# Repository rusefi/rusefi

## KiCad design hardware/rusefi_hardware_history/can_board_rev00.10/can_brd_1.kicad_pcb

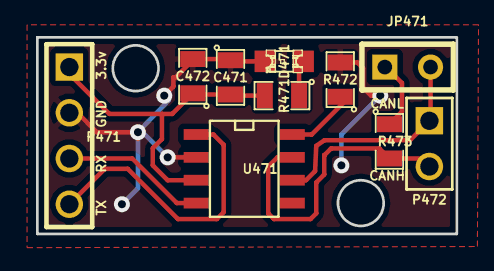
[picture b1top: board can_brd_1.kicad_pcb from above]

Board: 2 copper layers, 23.3 x 10.9 mm, 11 parts (1 on the bottom side), 9 nets.

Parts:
C471: .1uF; SM0805
C472: 4.7uF; SM0805
D471: RED; LED-0805
G471: LOGO; LOGO_F
JP471: JUMPER; SIL-2
P471: CONN_4; PIN_ARRAY_4x1
P472: CONN_2; PIN_ARRAY_2_A
R471: 1k; SM0805
R472: 10k; SM0805
R473: 120; SM0805
U471: SN65HVD230; SO8E

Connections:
/3.3V: C471.2, C472.1, P471.1, R471.2, U471.3
/CANH: P472.2, R473.2, U471.7
/CANL: JP471.2, P472.1, U471.6
/CAN_RX: P471.3, U471.4
/CAN_TX: P471.4, U471.1
GND: C471.1, C472.2, D471.2, P471.2, R472.2, U471.2
unnamed: R472.1, U471.8
unnamed: JP471.1, R473.1
unnamed: D471.1, R471.1

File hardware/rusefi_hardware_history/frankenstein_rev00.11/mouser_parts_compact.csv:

### this file was generated by rusEfi bom_builder on Sat Mar 08 11:58:11 CST 2014
### 292 components in 2047 lines of frankenstein.cmp
### 65 kinds of components in input file
### 5 entries in BOM dictionary bom_dictionary_mouser.csv
### 0 entries in ignore list
### no BOM record for 1pin_CONN_1
### no BOM record for LED-0805_GREEN
### no BOM record for LED-0805_LED
### no BOM record for LED-0805_RED
### no BOM record for LED-1206_LED
### no BOM record for LOGO_F_LOGO
### no BOM record for LOGO_LOGO
### no BOM record for MICRO-SDCARD-CONNECTOR-3300060P1_MICRO-SDCARD-CONNECTOR-3300060P1
### no BOM record for OSTVN06A150_CONN_6
### no BOM record for PIN_ARRAY-6X1_CONN_6
### no BOM record for PIN_ARRAY_10X2_CONN_10X2
### no BOM record for PIN_ARRAY_10X2_M_CONN_10X2
### no BOM record for PIN_ARRAY_1_CONN_1
### no BOM record for PIN_ARRAY_2X1_CONN_2
### no BOM record for PIN_ARRAY_2_A_CONN_2
### no BOM record for PIN_ARRAY_2_A_JUMPER
### no BOM record for PIN_ARRAY_3X1_CONN_3
### no BOM record for PIN_ARRAY_3_A_CONN_3
### no BOM record for PIN_ARRAY_4x1_CONN_4
### no BOM record for PIN_ARRAY_5x2_CONN_5X2
### no BOM record for SIL-16_3.5MM_CONN_16
### no BOM record for SIL-2_0R
### no BOM record for SIL-2_CONN_2
### no BOM record for SIL-2_DIODE
### no BOM record for SIL-2_JUMPER
### no BOM record for SIL-2_OPT
### no BOM record for SIL-2_TEST
### no BOM record for SM0805_.1uF
### no BOM record for SM0805_0.01uF
### no BOM record for SM0805_0.1uF
### no BOM record for SM0805_100
### no BOM record for SM0805_1000pF
### no BOM record for SM0805_10K
### no BOM record for SM0805_10k
### no BOM record for SM0805_10uF
### no BOM record for SM0805_120
### no BOM record for SM0805_1500
### no BOM record for SM0805_1K
### no BOM record for SM0805_1M
### no BOM record for SM0805_1k
### no BOM record for SM0805_1uF
### no BOM record for SM0805_20K
### no BOM record for SM0805_20R
### no BOM record for SM0805_2700
### no BOM record for SM0805_4.7uF
### no BOM record for SM0805_4700pF
### no BOM record for SM0805_47pF
### no BOM record for SM0805_500K
### no BOM record for SM0805_5k
### no BOM record for SM0805_LED
### no BOM record for SM1206_LED
### no BOM record for SO8E_ST_OVP_DRIVER
### no BOM record for SOD-123_DIODE
### no BOM record for bornier3_CONN_3
### no BOM record for msoic-8_TC4427AVOA
### no BOM record for pin_array_10x2_CONN_10X2
### no BOM record for pin_array_3x2_CONN_3X2
### no BOM record for pin_array_4x2_CONN_4X2
### no BOM record for sot23_DOUBLE_SCHOTTKY
### no BOM record for uMAX-uSOP_10_MAX9939




1,656-DX2R005HN2E700,mini USB socket
1,296-11654-1-ND,CAN driver
1,700-MAX9926UAEE,VR chip
3,595-LMV324IDR,quad op-amp
1,895-FT232RL,USB TTL chip

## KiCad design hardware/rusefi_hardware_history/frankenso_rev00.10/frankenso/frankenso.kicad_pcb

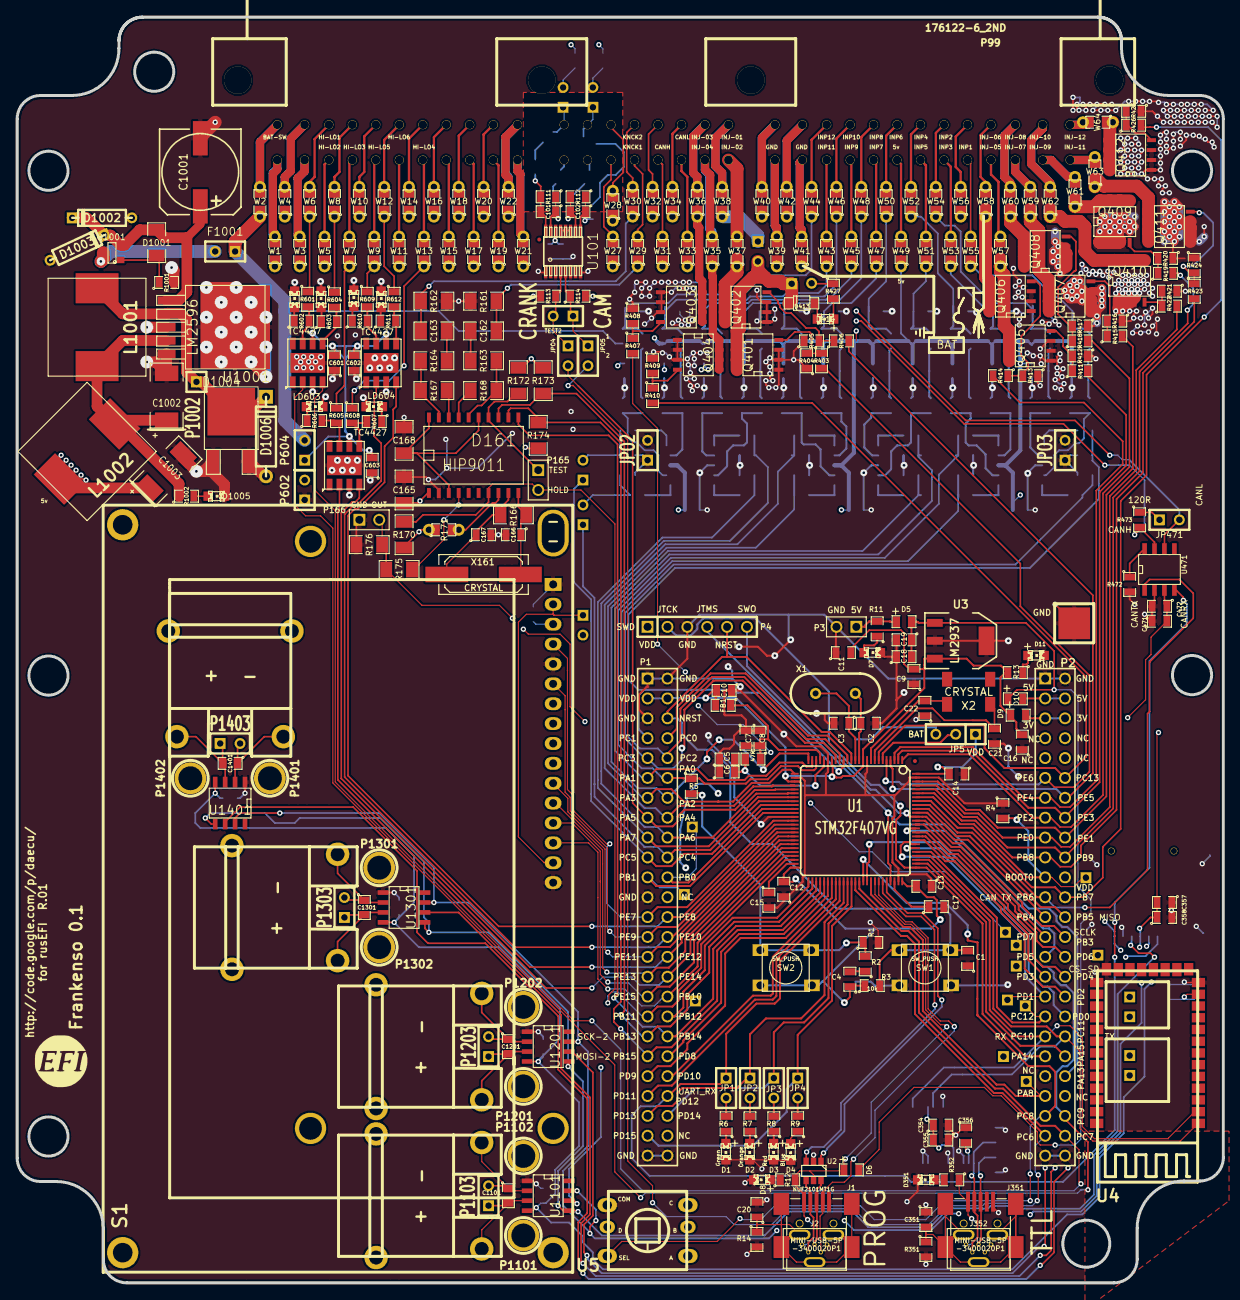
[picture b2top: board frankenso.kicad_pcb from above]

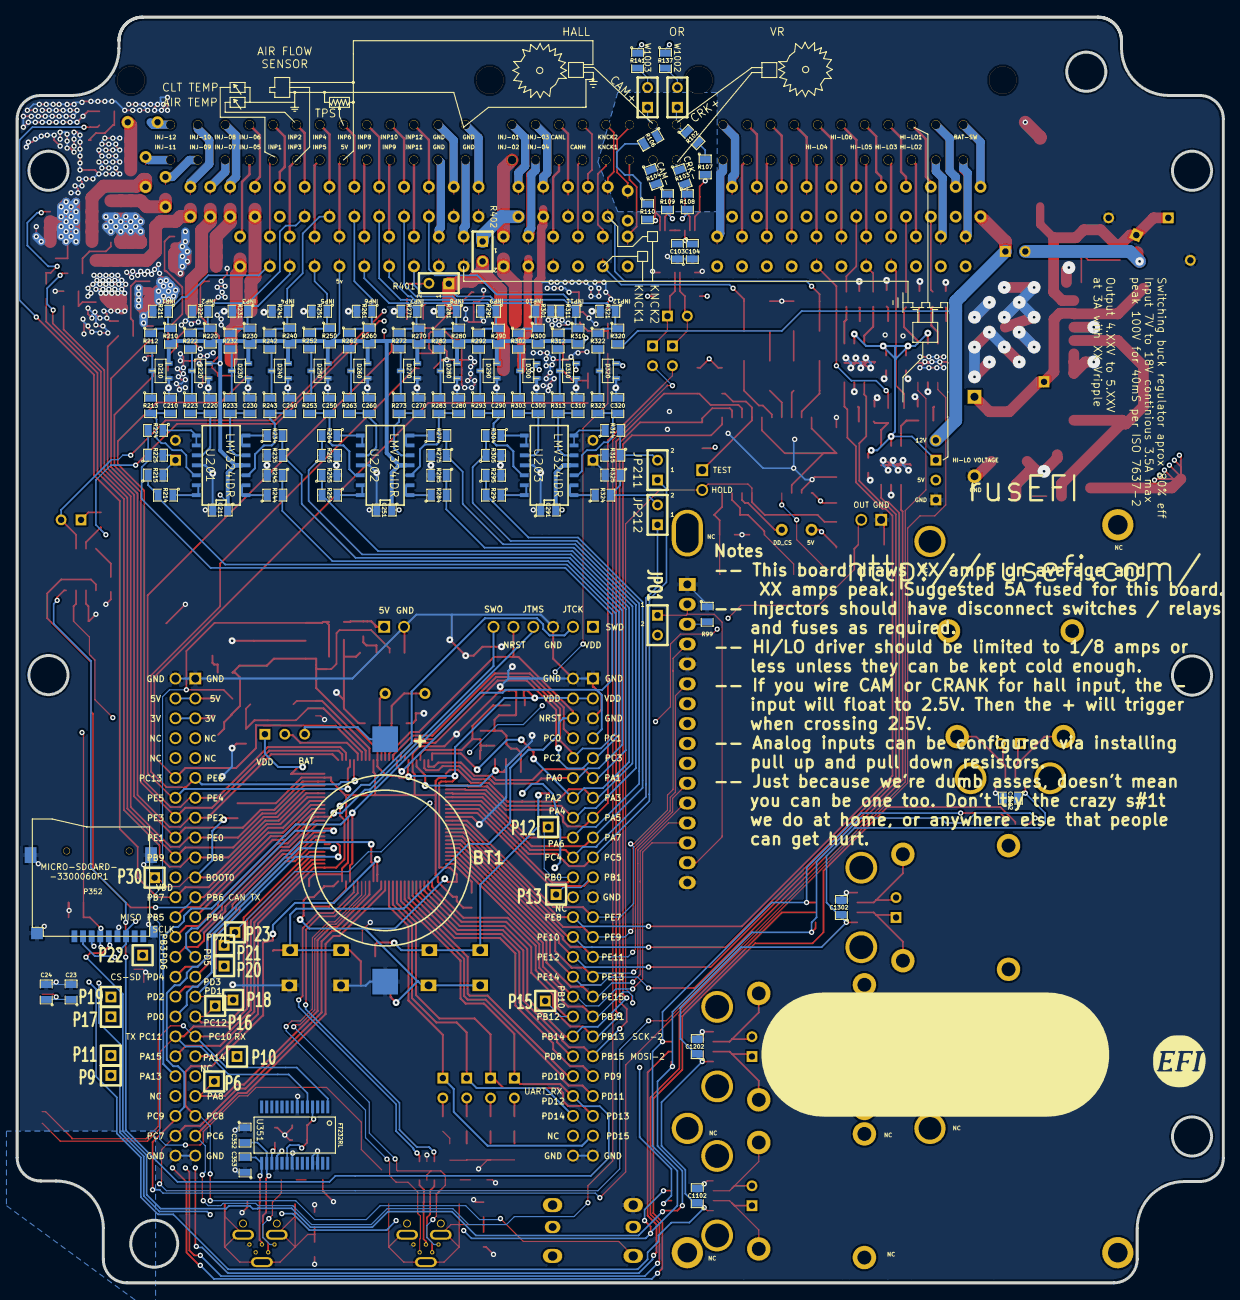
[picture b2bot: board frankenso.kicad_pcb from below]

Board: 4 copper layers, 154.1 x 161.7 mm, 441 parts (150 on the bottom side), 324 nets.

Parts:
BT1: BATTERY_CR2032; BATT_CR2032_MPD
C1: 0.02uF; SM0805
C2, C3, C21, C22: 18pF; SM0805
C4, C15, C17: 2u2F; SM0805
C5, C8, C210, C220, C230, C240, C250, C260, C270, C280, C290, C300, C310, C320: 0.01uF; SM0805
C6, C7, C16, C23: 1uF; SM0805
C9, C10, C11, C12, C13, C14, C18, C20, C104, C211, C251, C291, C601, C602, C603: 0.1uF; SM0805
C19, C354, C358, C472: 4.7uF; SM0805
C24, C355, C356, C357, C471: .1uF; SM0805
C101, C102: 1000pF; SM0805
C103: 10uF; SM0805
C162, C163: 47n; SM1206
C165: 100n; SM1206
C166, C167: 20pF; SM0805
C168: 22n; SM1206
C351: 4700pF; SM0805
C352, C353: 47pF; SM0805
C1001: 470uF 25V; SMDSVP10
C1002, C1003: 220uF 16V; SM2512
C1101, C1201, C1301, C1401: 10nF; SM0805-SM0603
C1102, C1202, C1302, C1402: 100nF; SM0805-SM0603
D1, D2, D3, D4, D7, D8, D11, D414: LED_0805; LED-0805_A
D5, D6, D9, D10: DIODESCH; SM0805-diode
D161: HIP9011; SO20L
D210, D220, D230, D240, D250, D260, D270, D280, D290, D300, D310, D320: DOUBLE_SCHOTTKY; sot23
D351: GREEN; LED-0805_A
D413: DIODE; SOD-123
D1001: ZENERSMALL; SM1206
D1002, D1003: TVS; D3
D1004: SCHDPAK; DPAK2
D1005: GREEN; LED-0805
D1006: DIODESCH; D4
F1001: 3.5A; SIL-2
FB1: FILTER; SM0805
G1: LOGO; LOGO_F
G2: LOGO
J1, J351: MINI-USB-5P-3400020P1
J2, J352: MINI-USB-5P-3400020P1; MINI-USB_RCTP_V-T_B
JP1, JP2, JP3, JP4, JP471: JUMPER; JUMPER-2
JP5: JUMPER3; SIL-3
JP211, JP212: TEST; SIL-2
JPO1, JPO2, JPO3, JPO4, JPO5: TEST; SIL-2
L1001, L1002: 38uH; SM100uH
LD601, LD602, LD603, LD604, LD605, LD606: LED; LED-0805
P1, P2: CONN_25X2; PIN_ARRAY_25x2_A
P3: CONN_2; PIN_ARRAY_2_A
P4: CONN_6; PIN_ARRAY-6X1
P5: CONN_1; 1PIN_SMD
P6, P9, P10, P11, P12, P13, P15, P16, P17, P18, P19, P20, P21, P22, P23, P30, P1002: CONN_1; SIL-1
P99: 176122-6_2ND; 176122-6_2nd
P165, P166: CONN_2; PIN_ARRAY_2X1
P352: MICRO-SDCARD-CONNECTOR-3300060P1
P602, P604, P1103, P1203, P1303, P1403: CONN_2; SIL-2
P1101, P1102, P1201, P1202, P1301, P1302, P1401, P1402: CONN_1; 1pin
P1104, P1204, P1304, P1404: CONN_2; tcpl_PCC-SMP
Q401, Q402, Q403, Q404, Q405, Q406, Q407, Q408, Q409, Q410, Q411, Q412: OVP_DRIVER; SO8E_ST
Q1001: MOS_PRO; SOT23
R1, R3, R4, R113, R114, R212, R222, R232, R242, R252, R262, R272, R282, R292, R302, R312, R321, R322, R472: 10k; SM0805
R2: 100R; SM0805
R5: 330R; SM0805
R6, R7, R8, R9: 680R; SM0805
R10: 47R; SM0805
R11, R12, R13, R352, R1001, R1002: 1k; SM0805
R14: 100k; SM0805
R99: 2K; SM0805
R102, R103, R104, R106, R107, R108, R109, R110, R111, R112: 5k; SM0805
R137, R141, R404, R405, R408, R409, R412, R413, R416, R417, R420, R421, R424, R425, R427: 1K; SM0805
R161, R162, R166: 1M; SM1206
R163, R164, R175, R176: 10k; SM1206
R167, R168: 68k; SM1206
R170, R172, R173, R174: 1K; SM1206
R171: 1K; SM0805_jumper
R210, R220, R230, R240, R250, R260, R270, R280, R290, R300, R310, R602, R603, R606, R607, R610, R611: 2700; SM0805
R211, R221, R231, R241, R251, R261, R271, R281, R291, R301, R311: 500K; SM0805
R213, R223, R233, R243, R253, R263, R273, R283, R293, R303, R313, R323, R601, R604, R605, R608, R609, R612: 100; SM0805
R214, R215, R224, R225, R234, R235, R244, R245, R254, R255, R264, R265, R274, R275, R284, R285, R294, R295, R304, R305, R314, R315, R324, R325: 1500; SM0805
R320: 39k; SM0805
R351: 1M; SM0805
R401: OPT; SIL-2
R402: 0R; SIL-2
R403, R406, R407, R410, R411, R414, R415, R418, R419, R422, R423, R426: 20R; SM0805
R473: 120; SM0805
S1: DISPLAY_BL; DISPLAY_4x20_BL
SW1, SW2: SW_PUSH; TL-1105
TEST2: TEST; SIL-2
U1: STM32F407VG; TQFP_100
U2: NUF2101MT1G; SOT-457
U3: LM2937; SOT223
U4: ITEAD_HC-0X; ITEAD_HC-05
U5: SKQUCAA010
U101: MAX9926/9927; maxim-10-QSOP16
U201, U202, U203: LMV324IDR; SO14N
U351: FT232RL; ssop-28
U471: SN65HVD230; SO8E
U601, U602, U603: TC4427; SOIC8-DFN
U1001: LM2596; DPAK5
U1101, U1201, U1301, U1401: MAX31855KASA; SO8E
W1, W2, W3, W4, W5, W6, W7, W8, W9, W10, W11, W12, W13, W14, W15, W16, W17, W18, W19, W20, W21, W22, W27, W28, W29, W30, W31, W32, W33, W34, W35, W36, W37, W38, W39, W40, W41, W42, W43, W44, W45, W46, W47, W48, W49, W50, W51, W52, W53, W54, W55, W56, W57, W58, W59, W60, W61, W62, W63, W64: TEST; SM0805_jumper
W1002, W1003: JMP; SIL-2
X1: CRYSTAL; HC-49V
X2: CRYSTAL; MC-306
X161: CRYSTAL; Q_49U3HMS

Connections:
/DD_HIP9011/5V: C4.1, C9.2, C10.2, C11.2, C12.2, C13.2, C14.2, C16.2, C23.1, C24.1, C103.2, C104.1, C165.1, C211.1, C251.1, C291.2, C354.1, C355.2, C1003.1, D9.1, D10.2, D161.1, D210.3, D220.3, D230.3, D240.3, D250.3, D260.3, D270.3, D280.3, D290.3, D300.3, D310.3, D320.3, FB1.2, JP5.1, JPO1.2, L1002.2, P1.3, P1.4, P2.3, P2.4, P2.22, P4.1, P602.2, R3.1, R13.2, R113.1, R114.2, R137.1, R141.1, R170.1, R171.1, R172.1, R173.1, R174.1, R210.2, R220.2, R230.2, R240.2, R250.2, R260.2, R270.2, R280.2, R290.2, R300.2, R310.2, SW2.2, U1.11, U1.19, U1.28, U1.50, U1.75, U1.100, U3.3, U4.12, U101.14, U201.4, U202.4, U203.4, U351.4, U351.20, W49.1
/DD_HIP9011/CS: D161.8, R171.2
/DD_HIP9011/INT/HLD: D161.7, P1.35, P165.2, R170.2, U1.48
/DD_HIP9011/INTOUT: D161.4, R175.1
/DD_HIP9011/KNOCK1: C162.1, R161.1, W29.1
/DD_HIP9011/KNOCK2: C163.1, R162.1, W30.1
/DD_HIP9011/OUT: P1.8, P166.2, R175.2, R176.1, U1.15
/DD_HIP9011/TEST: D161.14, P165.1, R172.2
/HD44780_VCC: JPO1.1, S1.2, S1.A
/PWR_buck_12V_switcher/FB: C1002.1, L1001.2, L1002.1, R1002.1, U1001.4
/PWR_buck_12V_switcher/OUT: D1004.2, D1006.2, L1001.1, P1002.1, U1001.2
/PWR_buck_12V_switcher/VBAT: C1001.1, D1001.2, D1002.2, D1003.2, Q1001.2, U1001.1
/PWR_buck_12V_switcher/Vf: F1001.2, Q1001.3
/adc_amp_divider/INP1: R210.1, R211.1, R212.1, W55.1
/adc_amp_divider/INP2: R220.1, R221.1, R222.1, W54.1
/adc_amp_divider/INP3: R230.1, R231.1, R232.1, W53.1
/adc_amp_divider/INP4: R240.1, R241.1, R242.1, W52.1
/adc_amp_divider/INP5: R250.1, R251.1, R252.1, W51.1
/adc_amp_divider/INP6: R260.1, R261.1, R262.1, W50.1
/adc_amp_divider/INP7: R270.1, R271.1, R272.1, W47.1
/adc_amp_divider/INP8: R280.1, R281.1, R282.1, W48.1
/adc_amp_divider/INP9: R290.1, R291.1, R292.1, W45.1
/adc_amp_divider/INP10: R300.1, R301.1, R302.1, W46.1
/adc_amp_divider/INP11: R310.1, R311.1, R312.1, W43.1
/adc_amp_divider/INP12: R320.1, R321.1, R322.1, W44.1
/adc_amp_divider/OUT1: P1.10, R214.2, R215.1, U1.17
/adc_amp_divider/OUT2: P1.7, R224.2, R225.1, U1.16
/adc_amp_divider/OUT3: P1.12, R5.1, R234.2, R235.1, U1.23
/adc_amp_divider/OUT4: P1.9, R244.2, R245.1, U1.18
/adc_amp_divider/OUT5: P1.14, R254.2, R255.1, U1.25
/adc_amp_divider/OUT6: P1.11, R264.2, R265.1, U1.24
/adc_amp_divider/OUT7: P1.16, R274.2, R275.1, U1.29
/adc_amp_divider/OUT8: P1.13, R284.2, R285.1, U1.26
/adc_amp_divider/OUT9: P1.17, R294.2, R295.1, U1.32
/adc_amp_divider/OUT10: P1.18, R304.2, R305.1, U1.31
/adc_amp_divider/OUT11: JP211.1, P1.19, U1.34
/adc_amp_divider/OUT12: JP212.1, P1.20, U1.33
/can_brd_1/3.3V: C357.2, C358.1, C471.2, C472.1, C1102.1, C1202.1, C1302.1, C1402.1, D9.2, P2.5, P2.6, P352.4, U471.3, U1101.4, U1201.4, U1301.4, U1401.4
/can_brd_1/CANH: R473.2, U471.7, W33.1
/can_brd_1/CANL: JP471.2, U471.6, W34.1
/can_brd_1/CAN_RX: JP1.1, P1.44, U1.59, U471.4
/can_brd_1/CAN_TX: P2.23, U1.92, U471.1
/cps_vrs_io_1/CAM: JPO5.1, R114.1, TEST2.1, U101.5
/cps_vrs_io_1/CAM+: P99.32, R106.1, W1003.1
/cps_vrs_io_1/CAM-: P99.24, R104.1
/cps_vrs_io_1/CRANK: JPO4.1, R113.2, TEST2.2, U101.4
/cps_vrs_io_1/CRK2+: P99.31, R102.1, W1002.1
/cps_vrs_io_1/CRK2-: P99.23, R103.1
/hi-lo/12V: F1001.1, P604.2, R320.2, W2.1
/hi-lo/HL1: R601.1, W6.1
/hi-lo/HL2: R604.1, W8.1
/hi-lo/HL3: R605.1, W7.1
/hi-lo/HL4: R608.1, W13.1
/hi-lo/HL5: R609.1, W9.1
/hi-lo/HL6: R612.1, W12.1
/hi-lo/H_IN1: P2.48, U1.64, U601.4
/hi-lo/H_IN2: P1.32, U1.45, U602.2
/hi-lo/H_IN3: P2.46, U1.66, U601.2
/hi-lo/H_IN4: P1.30, U1.43, U602.4
/hi-lo/H_IN5: P1.26, U1.39, U603.4
/hi-lo/H_IN6: P1.28, U1.41, U603.2
/hi-lo/VP: C601.2, C602.2, C603.2, P604.1, U601.6, U602.6, U603.6
/inj_12ch/5V: R401.2, R427.1
/inj_12ch/INJ-01: D413.2, Q401.2, R401.1, R402.2
/inj_12ch/INJ-01_2: R402.1, W38.1
/inj_12ch/INJ-01_5V: P2.11, R403.2, U1.5
/inj_12ch/INJ-02: Q402.2, W37.1
/inj_12ch/INJ-02_5V: P2.14, R406.2, U1.4
/inj_12ch/INJ-03: Q403.2, W36.1
/inj_12ch/INJ-03_5V: P2.27, P23.1, R407.2, U1.88
/inj_12ch/INJ-04: Q404.2, W35.1
/inj_12ch/INJ-04_5V: P2.12, R410.2, U1.7
/inj_12ch/INJ-05: Q405.2, W57.1
/inj_12ch/INJ-05_5V: P2.16, R411.2, U1.2
/inj_12ch/INJ-06: Q406.2, W58.1
/inj_12ch/INJ-06_5V: P2.13, R414.2, U1.3
/inj_12ch/INJ-07: Q407.2, W59.1
/inj_12ch/INJ-07_5V: P2.18, R415.2, U1.98
/inj_12ch/INJ-08: Q408.2, W60.1
/inj_12ch/INJ-08_5V: P2.15, R418.2, U1.1
/inj_12ch/INJ-09: Q409.2, W61.1
/inj_12ch/INJ-09_5V: P2.20, R419.2, U1.96
/inj_12ch/INJ-10: Q410.2, W62.1
/inj_12ch/INJ-10_5V: P2.17, R422.2, U1.97
/inj_12ch/INJ-11: Q411.2, W63.1
/inj_12ch/INJ-11_5V: P2.19, R423.2, U1.95
/inj_12ch/INJ-12: Q412.2, W64.1
/inj_12ch/INJ-12_5V: P2.24, R426.2, U1.93
/mmc_usb_1/CS_SD_MODULE: P2.32, P352.2, U1.85
/mmc_usb_1/D+: C353.2, J351.3, J352.3, U351.15
/mmc_usb_1/D-: C352.2, J351.2, J352.2, U351.16
/mmc_usb_1/shield: C351.2, J351.6, J352.6, R351.1
/stm32f407_board/5Vi: C18.2, C19.1, D5.2, D6.2, D10.1, U3.1
/stm32f407_board/BOOT0: P2.21, P30.1, R4.2, U1.94
/stm32f407_board/D+: J1.3, J2.3, U2.6
/stm32f407_board/D-: J1.2, J2.2, U2.4
/stm32f407_board/NRST: C1.2, P1.6, P4.5, R3.2, SW1.1, U1.14
/stm32f407_board/PA5: JPO4.2, P1.15, U1.30
/stm32f407_board/PA9: D6.1, J1.1, J2.1, R12.2, U1.68, U2.5
/stm32f407_board/PA10: J1.4, J2.4, U1.69
/stm32f407_board/PA11: U1.70, U2.3
/stm32f407_board/PA12: U1.71, U2.1
/stm32f407_board/PA15: P2.40, P11.1, U1.77
/stm32f407_board/PB0: P1.22, P12.1, U1.35
/stm32f407_board/PB1: P1.21, P13.1, U1.36
/stm32f407_board/PB3: P2.28, P4.6, P352.5, U1.89, U1101.5, U1201.5, U1301.5, U1401.5
/stm32f407_board/PB4: P2.25, P352.3, U1.90
/stm32f407_board/PB10: P1.34, S1.14, U1.47
/stm32f407_board/PB13: D161.13, P1.37, R173.2, U1.52
/stm32f407_board/PB14: D161.11, P1.38, U1.53
/stm32f407_board/PB15: D161.12, P1.39, R174.2, U1.54
/stm32f407_board/PC6: JPO5.2, P2.47, U1.63
/stm32f407_board/PC8: P2.45, U1.65, U5.6
/stm32f407_board/PC10: P2.37, U1.78, U4.2, U351.1
/stm32f407_board/PC11: P2.38, U1.79, U4.1, U351.5
/stm32f407_board/PC12: P2.35, P16.1, U1.80
/stm32f407_board/PD0: P2.36, P17.1, U1.81
/stm32f407_board/PD1: P2.33, P18.1, U1.82
/stm32f407_board/PD2: P2.34, P19.1, U1.83
/stm32f407_board/PD3: P2.31, P20.1, U1.84
/stm32f407_board/PD5: P2.29, P21.1, U1.86
/stm32f407_board/PD6: P2.30, P22.1, U1.87
/stm32f407_board/PD8: P1.40, U1.55, U5.1
/stm32f407_board/PD9: P1.41, U1.56, U5.3
/stm32f407_board/PD10: P1.42, U1.57, U5.2
/stm32f407_board/PD11: P1.43, U1.58, U5.5
/stm32f407_board/PD13: JP2.1, P1.45, U1.60
/stm32f407_board/PD14: JP3.1, P1.46, U1.61
/stm32f407_board/PD15: JP4.1, P1.47, U1.62
/stm32f407_board/PE7: P1.25, S1.4, U1.38
/stm32f407_board/PE9: P1.27, S1.6, U1.40
/stm32f407_board/PE11: P1.29, S1.11, U1.42
/stm32f407_board/PE13: P1.31, S1.12, U1.44
/stm32f407_board/PE15: P1.33, S1.13, U1.46
/stm32f407_board/shield: C20.1, J1.6, J2.6, R14.1
/thermocouple1//CS: P1.36, P15.1, U1.51, U1101.6
/thermocouple1/MISO: P2.26, P352.7, U1.91, U1101.7, U1201.7, U1301.7, U1401.7
/thermocouple1/TCPL+: C1101.2, P1103.1, P1104.2, U1101.3
/thermocouple1/TCPL-: C1101.1, P1103.2, P1104.1, U1101.2
/thermocouple2//CS: P2.39, P4.2, P10.1, U1.76, U1201.6
/thermocouple2/TCPL+: C1201.2, P1203.1, P1204.2, U1201.3
/thermocouple2/TCPL-: C1201.1, P1203.2, P1204.1, U1201.2
/thermocouple3//CS: P2.43, P6.1, U1.67, U1301.6
/thermocouple3/TCPL+: C1301.2, P1303.1, P1304.2, U1301.3
/thermocouple3/TCPL-: C1301.1, P1303.2, P1304.1, U1301.2
/thermocouple4//CS: P2.42, P4.4, P9.1, U1.72, U1401.6
/thermocouple4/TCPL+: C1401.2, P1403.1, P1404.2, U1401.3
/thermocouple4/TCPL-: C1401.1, P1403.2, P1404.1, U1401.2
GND: BT1.2, C1.1, C2.2, C3.2, C5.1, C6.1, C7.1, C8.1, C9.1, C10.1, C11.1, C12.1, C13.1, C14.1, C15.2, C16.1, C17.2, C18.1, C19.2, C20.2, C21.1, C22.1, C23.2, C24.2, C103.1, C104.2, C165.2, C166.2, C167.2, C168.2, C210.1, C211.2, C220.1, C230.1, C240.1, C250.1, C251.2, C260.1, C270.1, C280.1, C290.1, C291.1, C300.1, C310.1, C320.1, C351.1, C352.1, C353.1, C354.2, C355.1, C356.1, C357.1, C358.2, C471.1, C472.2, C601.1, C602.1, C603.1, C1001.2, C1002.2, C1003.2, C1102.2, C1202.2, C1302.2, C1402.2, D1.2, D2.2, D3.2, D4.2, D7.2, D8.2, D11.2, D161.2, D210.1, D220.1, D230.1, D240.1, D250.1, D260.1, D270.1, D280.1, D290.1, D300.1, D310.1, D320.1, D351.2, D1002.1, D1003.1, D1004.1, D1004.3, D1005.2, D1006.1, J1.5, J2.5, J351.5, J352.5, JPO2.1, JPO2.2, JPO3.1, JPO3.2, LD601.2, LD602.2, LD603.2, LD604.2, LD605.2, LD606.2, P1.1, P1.2, P1.5, P1.23, P1.49, P1.50, P2.1, P2.2, P2.49, P2.50, P3.2, P4.3, P5.1, P166.1, P352.6, P352.G1, P352.G2, P352.G3, P352.G4, P602.1, Q401.3, Q402.3, Q403.3, Q404.3, Q405.3, Q406.3, Q407.3, Q408.3, Q409.3, Q410.3, Q411.3, Q412.3, R1.2, R4.1, R14.2, R99.1, R161.2, R162.2, R176.2, R211.2, R215.2, R221.2, R225.2, R231.2, R235.2, R241.2, R245.2, R251.2, R255.2, R261.2, R265.2, R271.2, R275.2, R281.2, R285.2, R291.2, R295.2, R301.2, R305.2, R311.2, R315.2, R321.2, R325.2, R351.2, R404.1, R405.1, R408.1, R409.1, R412.1, R413.1, R416.1, R417.1, R420.1, R421.1, R424.1, R425.1, R472.2, R1001.2, S1.1, S1.5, S1.K, SW1.2, U1.10, U1.20, U1.27, U1.37, U1.74, U1.99, U2.2, U3.2, U3.4, U4.13, U4.21, U4.22, U5.4, U101.1, U101.3, U101.6, U101.8, U101.11, U101.12, U101.13, U201.11, U202.11, U203.11, U351.7, U351.18, U351.21, U351.25, U351.26, U471.2, U601.3, U601.9, U602.3, U602.9, U603.3, U603.9, U1001.3, U1001.5, U1101.1, U1201.1, U1301.1, U1401.1, W39.1, W40.1, W41.1, W42.1
unnamed: P99.35, W32.2
unnamed: P99.27, W31.2
unnamed: P99.34, W30.2
unnamed: P99.26, W29.2
unnamed: P99.15, W8.2
unnamed: P99.1, W1.2
unnamed: P99.12, W2.2
unnamed: P99.2, W3.2
unnamed: P99.13, W4.2
unnamed: P99.3, W5.2
unnamed: P99.14, W6.2
unnamed: P99.4, W7.2
unnamed: P99.5, W9.2
unnamed: P99.16, W10.2
unnamed: P99.6, W11.2
unnamed: P99.17, W12.2
unnamed: P99.7, W13.2
unnamed: P99.18, W14.2
unnamed: P99.8, W15.2
unnamed: P99.19, W16.2
unnamed: P99.9, W17.2
unnamed: P99.20, W18.2
unnamed: P99.10, W19.2
unnamed: P99.21, W20.2
unnamed: P99.11, W21.2
unnamed: P99.22, W22.2
unnamed: P99.51, W63.2
unnamed: P99.57, W50.2
unnamed: P99.45, W51.2
unnamed: P99.58, W52.2
unnamed: P99.46, W53.2
unnamed: P99.59, W54.2
unnamed: P99.47, W55.2
unnamed: P99.60, W56.2
unnamed: P99.48, W57.2
unnamed: P99.61, W58.2
unnamed: P99.49, W59.2
unnamed: P99.62, W60.2
unnamed: P99.50, W61.2
unnamed: P99.63, W62.2
unnamed: P99.44, W49.2
unnamed: P99.64, W64.2
unnamed: R99.2, S1.3
unnamed: P99.37, W36.2
unnamed: P99.25, W27.2
unnamed: P99.33, W28.2
unnamed: P99.28, W33.2
unnamed: P99.36, W34.2
unnamed: P99.29, W35.2
unnamed: P99.30, W37.2
unnamed: P99.38, W38.2
unnamed: P99.39, W39.2
unnamed: P99.52, W40.2
unnamed: P99.40, W41.2
unnamed: P99.53, W42.2
unnamed: P99.41, W43.2
unnamed: P99.54, W44.2
unnamed: P99.42, W45.2
unnamed: P99.55, W46.2
unnamed: P99.43, W47.2
unnamed: P99.56, W48.2
unnamed: D414.1, R427.2
unnamed: Q410.1, R421.2, R422.1
unnamed: D413.1, D414.2
unnamed: Q408.1, R417.2, R418.1
unnamed: Q406.1, R413.2, R414.1
unnamed: Q404.1, R409.2, R410.1
unnamed: Q402.1, R405.2, R406.1
unnamed: Q401.1, R403.1, R404.2
unnamed: Q405.1, R411.1, R412.2
unnamed: Q403.1, R407.1, R408.2
unnamed: Q412.1, R425.2, R426.1
unnamed: Q407.1, R415.1, R416.2
unnamed: Q409.1, R419.1, R420.2
unnamed: Q411.1, R423.1, R424.2
unnamed: C320.2, R323.2, U203.3
unnamed: JP211.2, R314.2, R315.1
unnamed: R324.1, U203.1, U203.2
unnamed: JP212.2, R324.2, R325.1
unnamed: D320.2, R322.2, R323.1
unnamed: D310.2, R312.2, R313.1
unnamed: C310.2, R313.2, U203.5
unnamed: R314.1, U203.6, U203.7
unnamed: R214.1, U201.13, U201.14
unnamed: D280.2, R282.2, R283.1
unnamed: D270.2, R272.2, R273.1
unnamed: R224.1, U201.8, U201.9
unnamed: D300.2, R302.2, R303.1
unnamed: D290.2, R292.2, R293.1
unnamed: R234.1, U201.6, U201.7
unnamed: R274.1, U202.6, U202.7
unnamed: R264.1, U202.8, U202.9
unnamed: C290.2, R293.2, U203.12
unnamed: R294.1, U203.13, U203.14
unnamed: R304.1, U203.8, U203.9
unnamed: R254.1, U202.13, U202.14
unnamed: R244.1, U201.1, U201.2
unnamed: R284.1, U202.1, U202.2
unnamed: C270.2, R273.2, U202.5
unnamed: C220.2, R223.2, U201.10
unnamed: C230.2, R233.2, U201.5
unnamed: C210.2, R213.2, U201.12
unnamed: C240.2, R243.2, U201.3
unnamed: D230.2, R232.2, R233.1
unnamed: C280.2, R283.2, U202.3
unnamed: C250.2, R253.2, U202.12
unnamed: C260.2, R263.2, U202.10
unnamed: C300.2, R303.2, U203.10
unnamed: D250.2, R252.2, R253.1
unnamed: D260.2, R262.2, R263.1
unnamed: D220.2, R222.2, R223.1
unnamed: D210.2, R212.2, R213.1
unnamed: D240.2, R242.2, R243.1
unnamed: D351.1, R352.2
unnamed: J351.1, J352.1, R352.1
unnamed: C356.2, U351.17
unnamed: R472.1, U471.8
unnamed: JP471.1, R473.1
unnamed: R104.2, R109.1
unnamed: R102.2, R107.1
unnamed: R103.2, R108.1
unnamed: R106.2, R110.1
unnamed: C101.2, R107.2, R111.2, U101.16
unnamed: C102.2, R109.2, R112.2, U101.10
unnamed: C101.1, R108.2, R111.1, U101.15
unnamed: C102.1, R110.2, R112.1, U101.9
unnamed: R137.2, W1002.2
unnamed: R141.2, W1003.2
unnamed: R601.2, R602.2, U601.7
unnamed: R603.2, R604.2, U601.5
unnamed: R605.2, R606.2, U602.7
unnamed: LD603.1, R606.1
unnamed: LD605.1, R610.1
unnamed: R609.2, R610.2, U603.7
unnamed: R611.2, R612.2, U603.5
unnamed: LD606.1, R611.1
unnamed: R607.2, R608.2, U602.5
unnamed: LD602.1, R603.1
unnamed: LD604.1, R607.1
unnamed: LD601.1, R602.1
unnamed: C163.2, R164.1
unnamed: C162.2, R163.1
unnamed: D161.18, R167.1
unnamed: D161.16, R163.2, R168.2
unnamed: D161.19, R164.2, R167.2
unnamed: D161.17, R168.1
unnamed: C166.1, D161.10, R166.1, X161.2
unnamed: C167.1, D161.9, R166.2, X161.1
unnamed: C168.1, D161.3, D161.15, D161.20
unnamed: D1001.1, Q1001.1, R1001.1
unnamed: D1005.1, R1002.2
unnamed: C5.2, C6.2, R10.2, U1.21
unnamed: JP5.2, U1.6
unnamed: BT1.1, JP5.3
unnamed: D5.1, P3.1, R11.2
unnamed: R1.1, R2.2, R5.2, SW2.1
unnamed: D1.1, R6.1
unnamed: D2.1, R7.1
unnamed: D3.1, R8.1
unnamed: D4.1, R9.1
unnamed: JP1.2, R6.2
unnamed: JP2.2, R7.2
unnamed: JP3.2, R8.2
unnamed: JP4.2, R9.2
unnamed: D8.1, R12.1
unnamed: C22.2, U1.9, X2.1
unnamed: C21.2, U1.8, X2.2
unnamed: D7.1, R11.1
unnamed: D11.1, R13.1
unnamed: C3.1, U1.13, X1.1
unnamed: C17.1, U1.73
unnamed: C2.1, U1.12, X1.2
unnamed: C15.1, U1.49
unnamed: C4.2, R2.1
unnamed: C7.2, C8.2, FB1.1, R10.1, U1.22

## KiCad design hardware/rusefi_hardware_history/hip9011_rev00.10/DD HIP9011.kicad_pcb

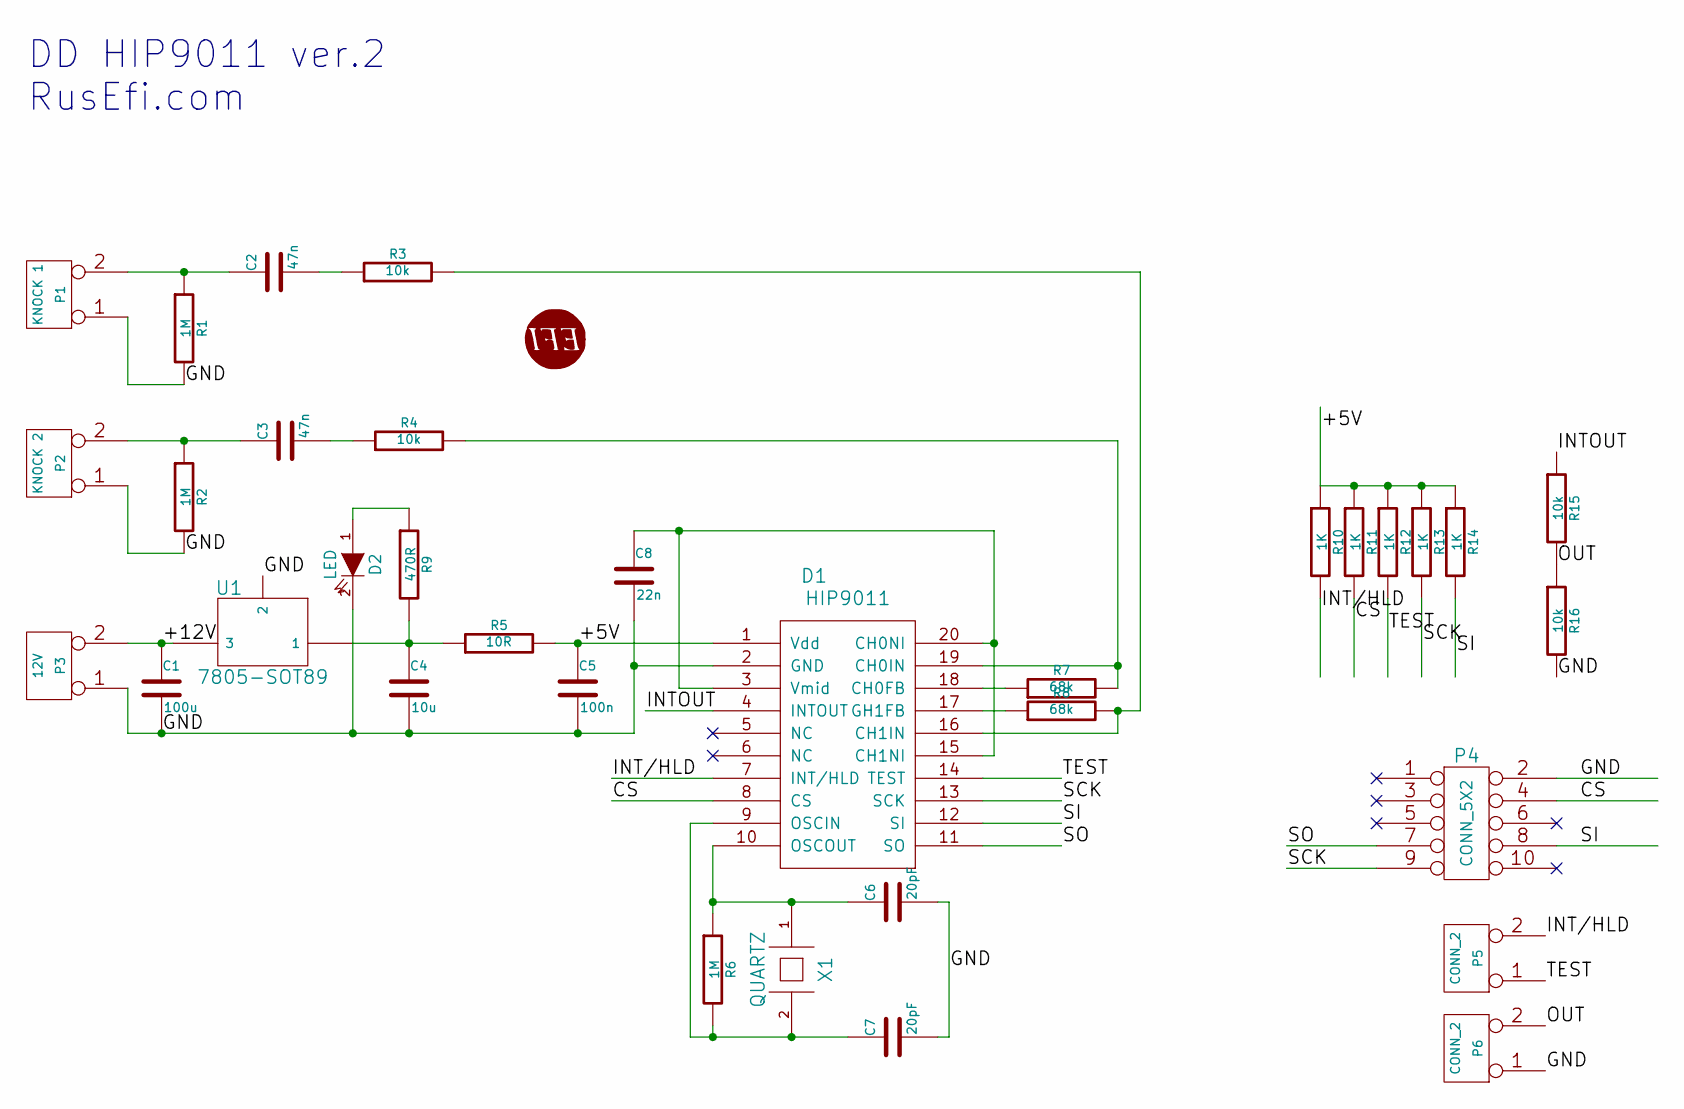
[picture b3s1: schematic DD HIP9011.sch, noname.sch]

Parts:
C1: 100u
C2, C3: 47n
C4: 10u
C5: 100n
C6, C7: 20pF
C8: 22n
D1: HIP9011
D2: LED
G1: LOGO
P1: KNOCK 1
P2: KNOCK 2
P3: 12V
P4: CONN_5X2
P5, P6: CONN_2
R1, R2, R6: 1M
R3, R4, R15, R16: 10k
R5: 10R
R7, R8: 68k
R9: 470R
R10, R11, R12, R13, R14: 1K
U1: 7805-SOT89
X1: QUARTZ

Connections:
/+5V: C5.1, D1.1 (Vdd), R5.2, R10.1, R11.1, R12.1, R13.1, R14.1
/+12V: C1.1, P3.2 (PM), U1.3
/CS: D1.8 (CS), P4.4, R11.2
/GND: C1.2, C4.2, C5.2, C6.2, C7.2, C8.2, D1.2 (GND), D2.2 (K), P1.1, P2.1, P3.1, P4.2, P6.1, R1.2, R2.2, R16.2, U1.2
/INT/HLD: D1.7 (INT/HLD), P5.2 (PM), R10.2
/INTOUT: D1.4 (INTOUT), R15.1
/OUT: P6.2 (PM), R15.2, R16.1
/SCK: D1.13 (SCK), P4.9, R13.2
/SI: D1.12 (SI), P4.8, R14.2
/SO: D1.11 (SO), P4.7
/TEST: D1.14 (TEST), P5.1, R12.2
unnamed: D2.1 (A), R9.1
unnamed: C4.1, R5.1, R9.2, U1.1
unnamed: C7.1, D1.9 (OSCIN), R6.2, X1.2
unnamed: C3.1, P2.2 (PM), R2.1
unnamed: C3.2, R4.1
unnamed: C6.1, D1.10 (OSCOUT), R6.1, X1.1
unnamed: C8.1, D1.3 (Vmid), D1.15 (CH1NI), D1.20 (CH0NI)
unnamed: D1.16 (CH1IN), R3.2, R8.2
unnamed: D1.17 (GH1FB), R8.1
unnamed: D1.18 (CH0FB), R7.1
unnamed: D1.19 (CH0IN), R4.2, R7.2
unnamed: C2.2, R3.1
unnamed: C2.1, P1.2 (PM), R1.1

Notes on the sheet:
DD HIP9011 ver.2 RusEfi.com

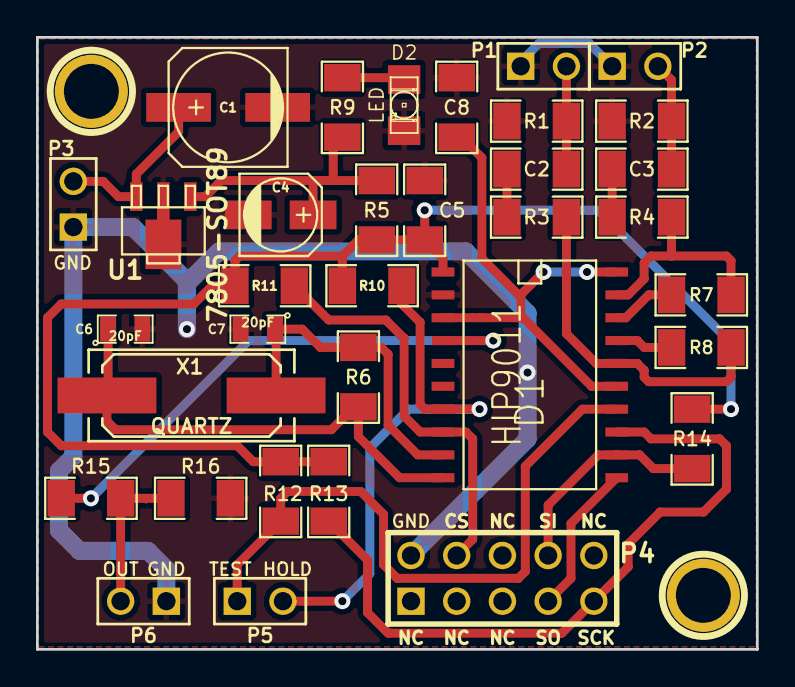
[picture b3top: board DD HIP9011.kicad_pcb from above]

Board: 2 copper layers, 40.0 x 34.0 mm, 35 parts (1 on the bottom side), 24 nets.
